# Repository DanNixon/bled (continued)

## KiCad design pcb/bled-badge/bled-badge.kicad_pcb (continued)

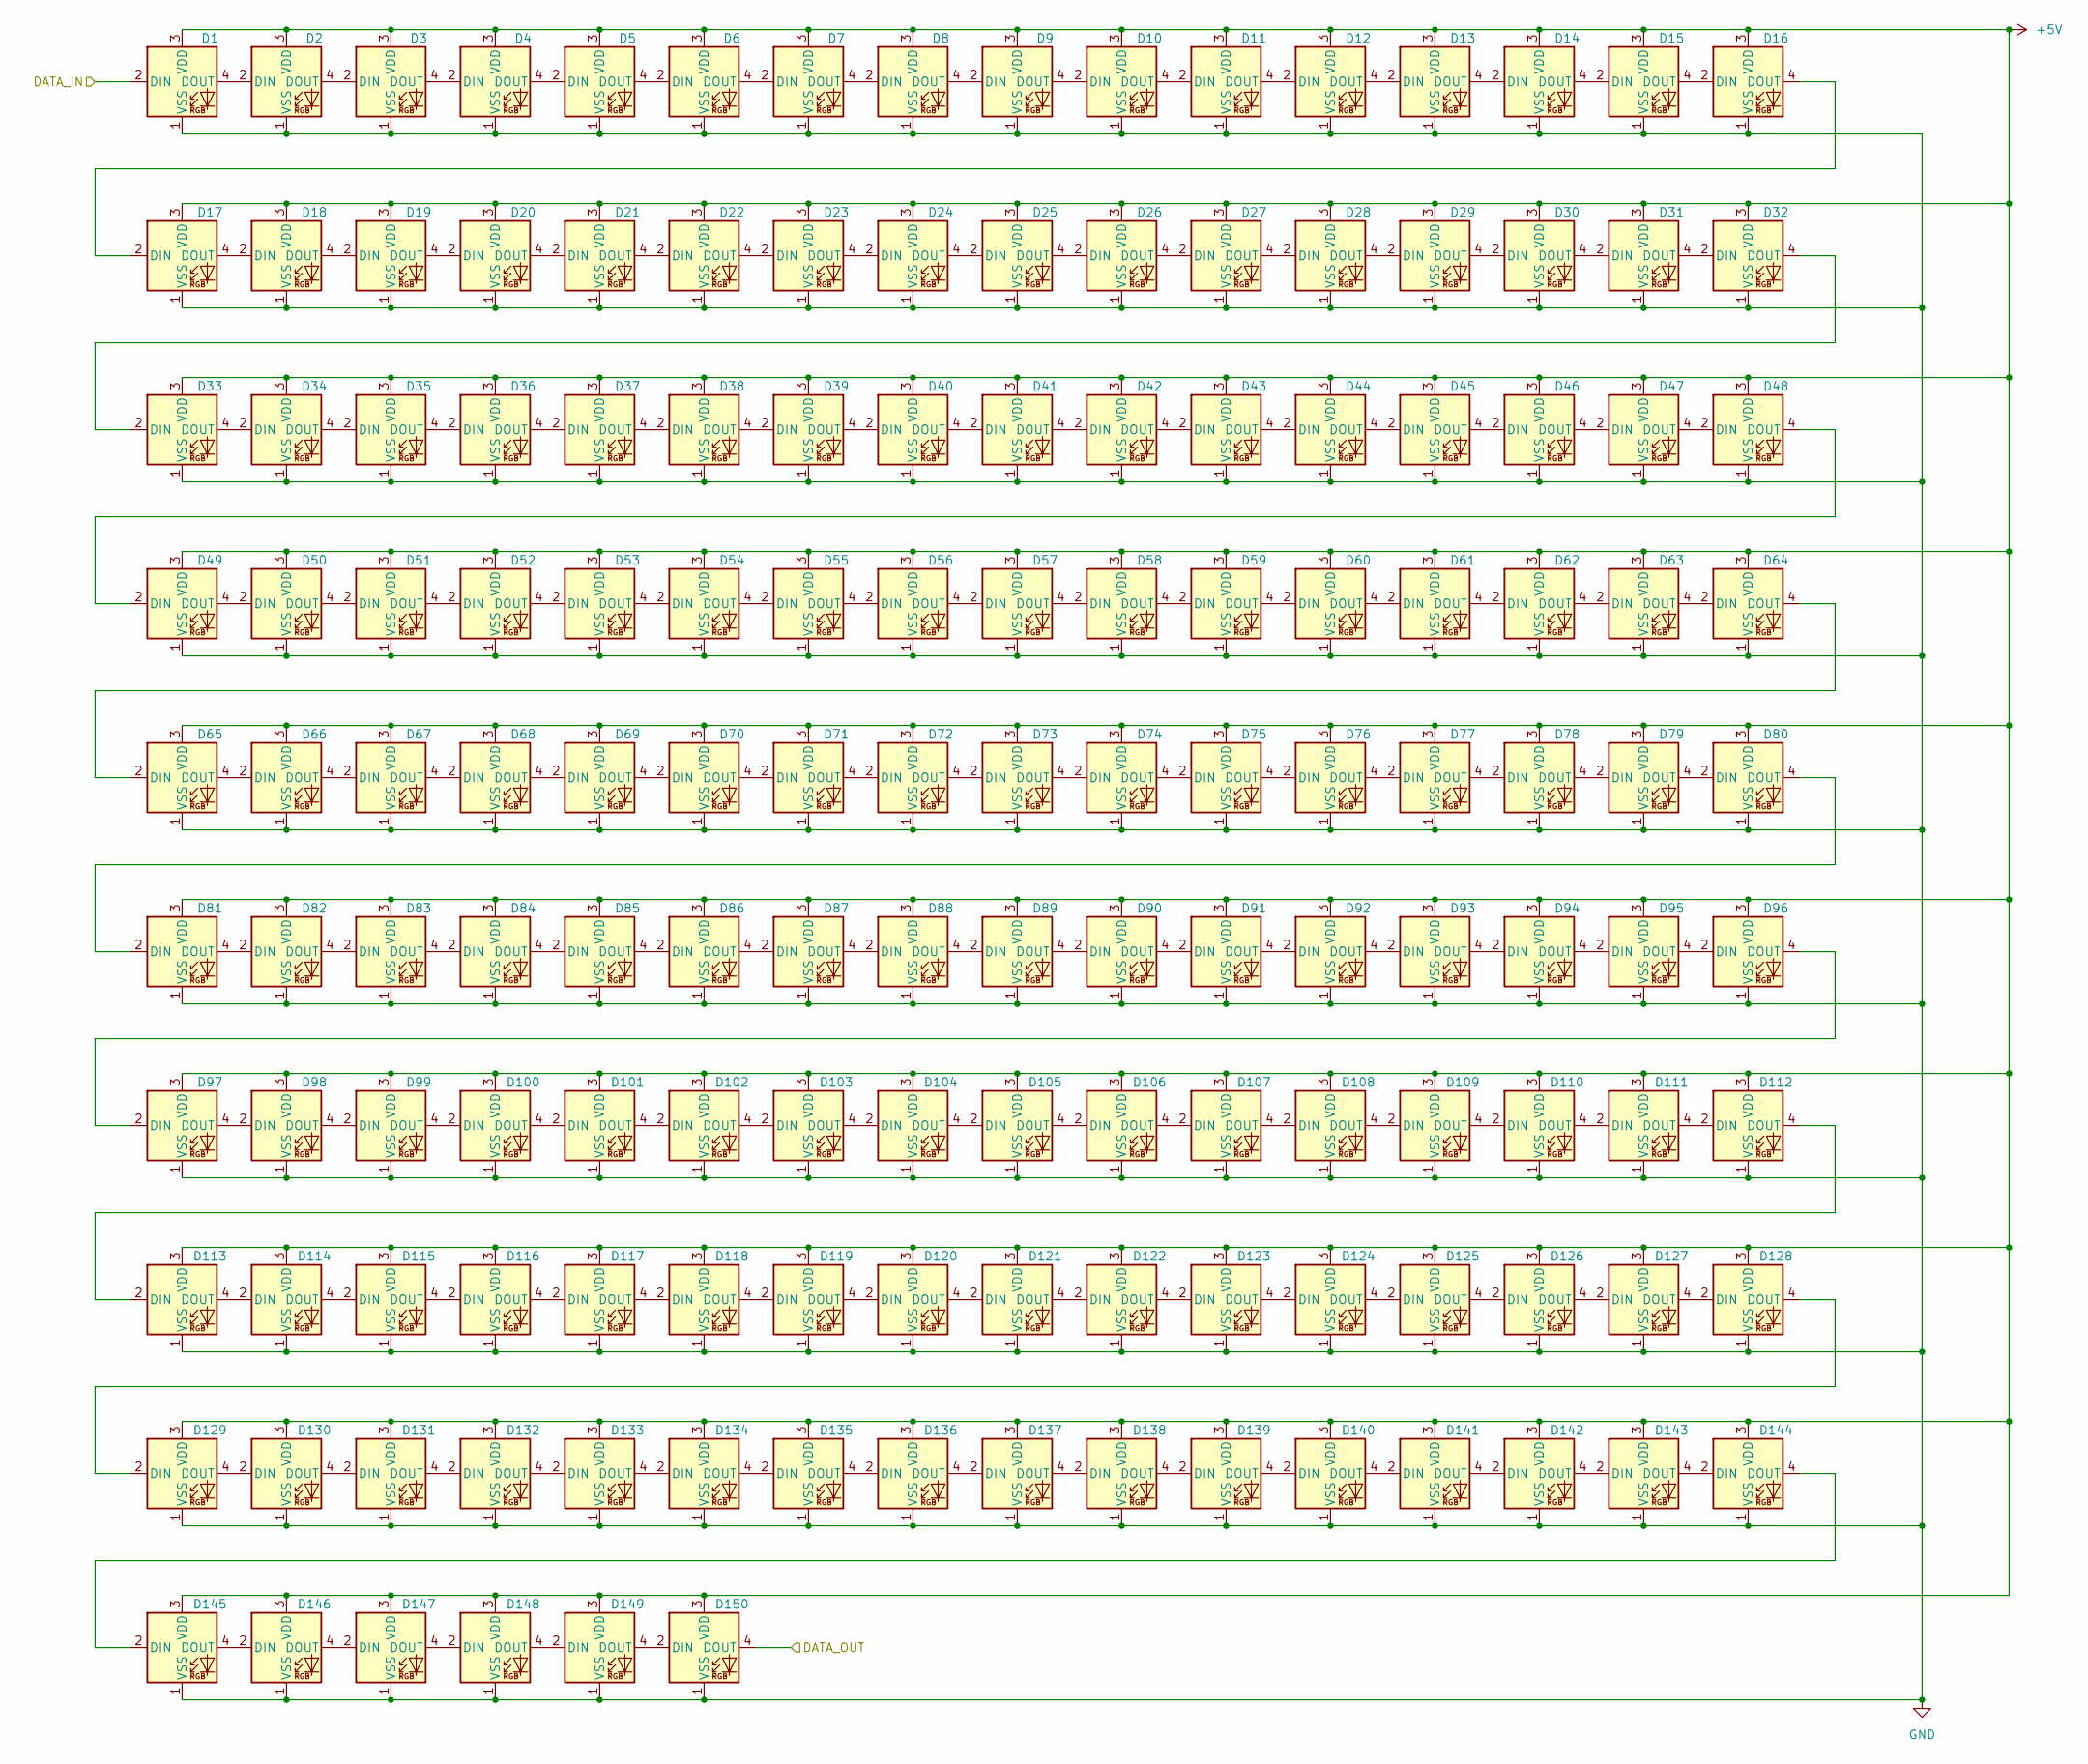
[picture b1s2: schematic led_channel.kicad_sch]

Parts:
D1, D2, D3, D4, D5, D6, D7, D8, D9, D10, D11, D12, D13, D14, D15, D16, D17, D18, D19, D20, D21, D22, D23, D24, D25, D26, D27, D28, D29, D30, D31, D32, D33, D34, D35, D36, D37, D38, D39, D40, D41, D42, D43, D44, D45, D46, D47, D48, D49, D50, D51, D52, D53, D54, D55, D56, D57, D58, D59, D60, D61, D62, D63, D64, D65, D66, D67, D68, D69, D70, D71, D72, D73, D74, D75, D76, D77, D78, D79, D80, D81, D82, D83, D84, D85, D86, D87, D88, D89, D90, D91, D92, D93, D94, D95, D96, D97, D98, D99, D100, D101, D102, D103, D104, D105, D106, D107, D108, D109, D110, D111, D112, D113, D114, D115, D116, D117, D118, D119, D120, D121, D122, D123, D124, D125, D126, D127, D128, D129, D130, D131, D132, D133, D134, D135, D136, D137, D138, D139, D140, D141, D142, D143, D144, D145, D146, D147, D148, D149, D150: XL-1615RGBC-WS2812B-S; XL-1615RGBC-2812B-S; LCSC C41413180

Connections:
+5V: D1.3 (VDD), D2.3 (VDD), D3.3 (VDD), D4.3 (VDD), D5.3 (VDD), D6.3 (VDD), D7.3 (VDD), D8.3 (VDD), D9.3 (VDD), D10.3 (VDD), D11.3 (VDD), D12.3 (VDD), D13.3 (VDD), D14.3 (VDD), D15.3 (VDD), D16.3 (VDD), D17.3 (VDD), D18.3 (VDD), D19.3 (VDD), D20.3 (VDD), D21.3 (VDD), D22.3 (VDD), D23.3 (VDD), D24.3 (VDD), D25.3 (VDD), D26.3 (VDD), D27.3 (VDD), D28.3 (VDD), D29.3 (VDD), D30.3 (VDD), D31.3 (VDD), D32.3 (VDD), D33.3 (VDD), D34.3 (VDD), D35.3 (VDD), D36.3 (VDD), D37.3 (VDD), D38.3 (VDD), D39.3 (VDD), D40.3 (VDD), D41.3 (VDD), D42.3 (VDD), D43.3 (VDD), D44.3 (VDD), D45.3 (VDD), D46.3 (VDD), D47.3 (VDD), D48.3 (VDD), D49.3 (VDD), D50.3 (VDD), D51.3 (VDD), D52.3 (VDD), D53.3 (VDD), D54.3 (VDD), D55.3 (VDD), D56.3 (VDD), D57.3 (VDD), D58.3 (VDD), D59.3 (VDD), D60.3 (VDD), D61.3 (VDD), D62.3 (VDD), D63.3 (VDD), D64.3 (VDD), D65.3 (VDD), D66.3 (VDD), D67.3 (VDD), D68.3 (VDD), D69.3 (VDD), D70.3 (VDD), D71.3 (VDD), D72.3 (VDD), D73.3 (VDD), D74.3 (VDD), D75.3 (VDD), D76.3 (VDD), D77.3 (VDD), D78.3 (VDD), D79.3 (VDD), D80.3 (VDD)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; also elsewhere on the board
/CH0_OUT: D150.4 (DOUT)
/CH3_IN: D1.2 (DIN); also elsewhere on the board
GND: D1.1 (VSS), D2.1 (VSS), D3.1 (VSS), D4.1 (VSS), D5.1 (VSS), D6.1 (VSS), D7.1 (VSS), D8.1 (VSS), D9.1 (VSS), D10.1 (VSS), D11.1 (VSS), D12.1 (VSS), D13.1 (VSS), D14.1 (VSS), D15.1 (VSS), D16.1 (VSS), D17.1 (VSS), D18.1 (VSS), D19.1 (VSS), D20.1 (VSS), D21.1 (VSS), D22.1 (VSS), D23.1 (VSS), D24.1 (VSS), D25.1 (VSS), D26.1 (VSS), D27.1 (VSS), D28.1 (VSS), D29.1 (VSS), D30.1 (VSS), D31.1 (VSS), D32.1 (VSS), D33.1 (VSS), D34.1 (VSS), D35.1 (VSS), D36.1 (VSS), D37.1 (VSS), D38.1 (VSS), D39.1 (VSS), D40.1 (VSS), D41.1 (VSS), D42.1 (VSS), D43.1 (VSS), D44.1 (VSS), D45.1 (VSS), D46.1 (VSS), D47.1 (VSS), D48.1 (VSS), D49.1 (VSS), D50.1 (VSS), D51.1 (VSS), D52.1 (VSS), D53.1 (VSS), D54.1 (VSS), D55.1 (VSS), D56.1 (VSS), D57.1 (VSS), D58.1 (VSS), D59.1 (VSS), D60.1 (VSS), D61.1 (VSS), D62.1 (VSS), D63.1 (VSS), D64.1 (VSS), D65.1 (VSS), D66.1 (VSS), D67.1 (VSS), D68.1 (VSS), D69.1 (VSS), D70.1 (VSS), D71.1 (VSS), D72.1 (VSS), D73.1 (VSS), D74.1 (VSS), D75.1 (VSS), D76.1 (VSS), D77.1 (VSS), D78.1 (VSS), D79.1 (VSS), D80.1 (VSS)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; also elsewhere on the board
unnamed: D1.4 (DOUT), D2.2 (DIN)
unnamed: D2.4 (DOUT), D3.2 (DIN)
unnamed: D3.4 (DOUT), D4.2 (DIN)
unnamed: D4.4 (DOUT), D5.2 (DIN)
unnamed: D5.4 (DOUT), D6.2 (DIN)
unnamed: D6.4 (DOUT), D7.2 (DIN)
unnamed: D7.4 (DOUT), D8.2 (DIN)
unnamed: D8.4 (DOUT), D9.2 (DIN)
unnamed: D9.4 (DOUT), D10.2 (DIN)
unnamed: D10.4 (DOUT), D11.2 (DIN)
unnamed: D11.4 (DOUT), D12.2 (DIN)
unnamed: D12.4 (DOUT), D13.2 (DIN)
unnamed: D13.4 (DOUT), D14.2 (DIN)
unnamed: D14.4 (DOUT), D15.2 (DIN)
unnamed: D15.4 (DOUT), D16.2 (DIN)
unnamed: D16.4 (DOUT), D17.2 (DIN)
unnamed: D17.4 (DOUT), D18.2 (DIN)
unnamed: D18.4 (DOUT), D19.2 (DIN)
unnamed: D19.4 (DOUT), D20.2 (DIN)
unnamed: D20.4 (DOUT), D21.2 (DIN)
unnamed: D21.4 (DOUT), D22.2 (DIN)
unnamed: D22.4 (DOUT), D23.2 (DIN)
unnamed: D23.4 (DOUT), D24.2 (DIN)
unnamed: D24.4 (DOUT), D25.2 (DIN)
unnamed: D25.4 (DOUT), D26.2 (DIN)
unnamed: D26.4 (DOUT), D27.2 (DIN)
unnamed: D27.4 (DOUT), D28.2 (DIN)
unnamed: D28.4 (DOUT), D29.2 (DIN)
unnamed: D29.4 (DOUT), D30.2 (DIN)
unnamed: D30.4 (DOUT), D31.2 (DIN)
unnamed: D31.4 (DOUT), D32.2 (DIN)
unnamed: D32.4 (DOUT), D33.2 (DIN)
unnamed: D33.4 (DOUT), D34.2 (DIN)
unnamed: D34.4 (DOUT), D35.2 (DIN)
unnamed: D35.4 (DOUT), D36.2 (DIN)
unnamed: D36.4 (DOUT), D37.2 (DIN)
unnamed: D37.4 (DOUT), D38.2 (DIN)
unnamed: D38.4 (DOUT), D39.2 (DIN)
unnamed: D39.4 (DOUT), D40.2 (DIN)
unnamed: D40.4 (DOUT), D41.2 (DIN)
unnamed: D41.4 (DOUT), D42.2 (DIN)
unnamed: D42.4 (DOUT), D43.2 (DIN)
unnamed: D43.4 (DOUT), D44.2 (DIN)
unnamed: D44.4 (DOUT), D45.2 (DIN)
unnamed: D45.4 (DOUT), D46.2 (DIN)
unnamed: D46.4 (DOUT), D47.2 (DIN)
unnamed: D47.4 (DOUT), D48.2 (DIN)
unnamed: D48.4 (DOUT), D49.2 (DIN)
unnamed: D49.4 (DOUT), D50.2 (DIN)
unnamed: D50.4 (DOUT), D51.2 (DIN)
unnamed: D51.4 (DOUT), D52.2 (DIN)
unnamed: D52.4 (DOUT), D53.2 (DIN)
unnamed: D53.4 (DOUT), D54.2 (DIN)
unnamed: D54.4 (DOUT), D55.2 (DIN)
unnamed: D55.4 (DOUT), D56.2 (DIN)
unnamed: D56.4 (DOUT), D57.2 (DIN)
unnamed: D57.4 (DOUT), D58.2 (DIN)
unnamed: D58.4 (DOUT), D59.2 (DIN)
unnamed: D59.4 (DOUT), D60.2 (DIN)
unnamed: D60.4 (DOUT), D61.2 (DIN)
unnamed: D61.4 (DOUT), D62.2 (DIN)
unnamed: D62.4 (DOUT), D63.2 (DIN)
unnamed: D63.4 (DOUT), D64.2 (DIN)
unnamed: D64.4 (DOUT), D65.2 (DIN)
unnamed: D65.4 (DOUT), D66.2 (DIN)
unnamed: D66.4 (DOUT), D67.2 (DIN)
unnamed: D67.4 (DOUT), D68.2 (DIN)
unnamed: D68.4 (DOUT), D69.2 (DIN)
unnamed: D69.4 (DOUT), D70.2 (DIN)
unnamed: D70.4 (DOUT), D71.2 (DIN)
unnamed: D71.4 (DOUT), D72.2 (DIN)
unnamed: D72.4 (DOUT), D73.2 (DIN)
unnamed: D73.4 (DOUT), D74.2 (DIN)
unnamed: D74.4 (DOUT), D75.2 (DIN)
unnamed: D75.4 (DOUT), D76.2 (DIN)
unnamed: D76.4 (DOUT), D77.2 (DIN)
unnamed: D77.4 (DOUT), D78.2 (DIN)
unnamed: D78.4 (DOUT), D79.2 (DIN)
unnamed: D79.4 (DOUT), D80.2 (DIN)
unnamed: D80.4 (DOUT), D81.2 (DIN)
unnamed: D81.4 (DOUT), D82.2 (DIN)
unnamed: D82.4 (DOUT), D83.2 (DIN)
unnamed: D83.4 (DOUT), D84.2 (DIN)
unnamed: D84.4 (DOUT), D85.2 (DIN)
unnamed: D85.4 (DOUT), D86.2 (DIN)
unnamed: D86.4 (DOUT), D87.2 (DIN)
unnamed: D87.4 (DOUT), D88.2 (DIN)
unnamed: D88.4 (DOUT), D89.2 (DIN)
unnamed: D89.4 (DOUT), D90.2 (DIN)
unnamed: D90.4 (DOUT), D91.2 (DIN)
unnamed: D91.4 (DOUT), D92.2 (DIN)
unnamed: D92.4 (DOUT), D93.2 (DIN)
unnamed: D93.4 (DOUT), D94.2 (DIN)
unnamed: D94.4 (DOUT), D95.2 (DIN)
unnamed: D95.4 (DOUT), D96.2 (DIN)
unnamed: D96.4 (DOUT), D97.2 (DIN)
unnamed: D97.4 (DOUT), D98.2 (DIN)
unnamed: D98.4 (DOUT), D99.2 (DIN)
unnamed: D99.4 (DOUT), D100.2 (DIN)
unnamed: D100.4 (DOUT), D101.2 (DIN)
unnamed: D101.4 (DOUT), D102.2 (DIN)
unnamed: D102.4 (DOUT), D103.2 (DIN)
unnamed: D103.4 (DOUT), D104.2 (DIN)
unnamed: D104.4 (DOUT), D105.2 (DIN)
unnamed: D105.4 (DOUT), D106.2 (DIN)
unnamed: D106.4 (DOUT), D107.2 (DIN)
unnamed: D107.4 (DOUT), D108.2 (DIN)
unnamed: D108.4 (DOUT), D109.2 (DIN)
unnamed: D109.4 (DOUT), D110.2 (DIN)
unnamed: D110.4 (DOUT), D111.2 (DIN)
unnamed: D111.4 (DOUT), D112.2 (DIN)
unnamed: D112.4 (DOUT), D113.2 (DIN)
unnamed: D113.4 (DOUT), D114.2 (DIN)
unnamed: D114.4 (DOUT), D115.2 (DIN)
unnamed: D115.4 (DOUT), D116.2 (DIN)
unnamed: D116.4 (DOUT), D117.2 (DIN)
unnamed: D117.4 (DOUT), D118.2 (DIN)
unnamed: D118.4 (DOUT), D119.2 (DIN)
unnamed: D119.4 (DOUT), D120.2 (DIN)
unnamed: D120.4 (DOUT), D121.2 (DIN)
unnamed: D121.4 (DOUT), D122.2 (DIN)
unnamed: D122.4 (DOUT), D123.2 (DIN)
unnamed: D123.4 (DOUT), D124.2 (DIN)
unnamed: D124.4 (DOUT), D125.2 (DIN)
unnamed: D125.4 (DOUT), D126.2 (DIN)
unnamed: D126.4 (DOUT), D127.2 (DIN)
unnamed: D127.4 (DOUT), D128.2 (DIN)
unnamed: D128.4 (DOUT), D129.2 (DIN)
unnamed: D129.4 (DOUT), D130.2 (DIN)
unnamed: D130.4 (DOUT), D131.2 (DIN)
unnamed: D131.4 (DOUT), D132.2 (DIN)
unnamed: D132.4 (DOUT), D133.2 (DIN)
unnamed: D133.4 (DOUT), D134.2 (DIN)
unnamed: D134.4 (DOUT), D135.2 (DIN)
unnamed: D135.4 (DOUT), D136.2 (DIN)
unnamed: D136.4 (DOUT), D137.2 (DIN)
unnamed: D137.4 (DOUT), D138.2 (DIN)
unnamed: D138.4 (DOUT), D139.2 (DIN)
unnamed: D139.4 (DOUT), D140.2 (DIN)
unnamed: D140.4 (DOUT), D141.2 (DIN)
unnamed: D141.4 (DOUT), D142.2 (DIN)
unnamed: D142.4 (DOUT), D143.2 (DIN)
unnamed: D143.4 (DOUT), D144.2 (DIN)
unnamed: D144.4 (DOUT), D145.2 (DIN)
unnamed: D145.4 (DOUT), D146.2 (DIN)
unnamed: D146.4 (DOUT), D147.2 (DIN)
unnamed: D147.4 (DOUT), D148.2 (DIN)
unnamed: D148.4 (DOUT), D149.2 (DIN)
unnamed: D149.4 (DOUT), D150.2 (DIN)

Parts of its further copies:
D151, D152, D153, D154, D155, D156, D157, D158, D159, D160, D161, D162, D163, D164, D165, D166, D167, D168, D169, D170, D171, D172, D173, D174, D175, D176, D177, D178, D179, D180, D181, D182, D183, D184, D185, D186, D187, D188, D189, D190, D191, D192, D193, D194, D195, D196, D197, D198, D199, D200, D201, D202, D203, D204, D205, D206, D207, D208, D209, D210, D211, D212, D213, D214, D215, D216, D217, D218, D219, D220, D221, D222, D223, D224, D225, D226, D227, D228, D229, D230, D231, D232, D233, D234, D235, D236, D237, D238, D239, D240, D241, D242, D243, D244, D245, D246, D247, D248, D249, D250, D251, D252, D253, D254, D255, D256, D257, D258, D259, D260, D261, D262, D263, D264, D265, D266, D267, D268, D269, D270, D271, D272, D273, D274, D275, D276, D277, D278, D279, D280, D281, D282, D283, D284, D285, D286, D287, D288, D289, D290, D291, D292, D293, D294, D295, D296, D297, D298, D299, D300, D301, D302, D303, D304, D305, D306, D307, D308, D309, D310, D311, D312, D313, D314, D315, D316, D317, D318, D319, D320, D321, D322, D323, D324, D325, D326, D327, D328, D329, D330, D331, D332, D333, D334, D335, D336, D337, D338, D339, D340, D341, D342, D343, D344, D345, D346, D347, D348, D349, D350, D351, D352, D353, D354, D355, D356, D357, D358, D359, D360, D361, D362, D363, D364, D365, D366, D367, D368, D369, D370, D371, D372, D373, D374, D375, D376, D377, D378, D379, D380, D381, D382, D383, D384, D385, D386, D387, D388, D389, D390, D391, D392, D393, D394, D395, D396, D397, D398, D399, D400, D401, D402, D403, D404, D405, D406, D407, D408, D409, D410, D411, D412, D413, D414, D415, D416, D417, D418, D419, D420, D421, D422, D423, D424, D425, D426, D427, D428, D429, D430, D431, D432, D433, D434, D435, D436, D437, D438, D439, D440, D441, D442, D443, D444, D445, D446, D447, D448, D449, D450, D451, D452, D453, D454, D455, D456, D457, D458, D459, D460, D461, D462, D463, D464, D465, D466, D467, D468, D469, D470, D471, D472, D473, D474, D475, D476, D477, D478, D479, D480, D481, D482, D483, D484, D485, D486, D487, D488, D489, D490, D491, D492, D493, D494, D495, D496, D497, D498, D499, D500, D501, D502, D503, D504, D505, D506, D507, D508, D509, D510, D511, D512, D513, D514, D515, D516, D517, D518, D519, D520, D521, D522, D523, D524, D525, D526, D527, D528, D529, D530, D531, D532, D533, D534, D535, D536, D537, D538, D539, D540, D541, D542, D543, D544, D545, D546, D547, D548, D549, D550, D551, D552, D553, D554, D555, D556, D557, D558, D559, D560, D561, D562, D563, D564, D565, D566, D567, D568, D569, D570, D571, D572, D573, D574, D575, D576, D577, D578, D579, D580, D581, D582, D583, D584, D585, D586, D587, D588, D589, D590, D591, D592, D593, D594, D595, D596, D597, D598, D599, D600: XL-1615RGBC-WS2812B-S; XL-1615RGBC-2812B-S; LCSC C41413180

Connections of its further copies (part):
+5V: D151.3 (VDD), D152.3 (VDD), D153.3 (VDD), D154.3 (VDD), D155.3 (VDD), D156.3 (VDD), D157.3 (VDD), D158.3 (VDD), D159.3 (VDD), D160.3 (VDD), D161.3 (VDD), D162.3 (VDD), D163.3 (VDD), D164.3 (VDD), D165.3 (VDD), D166.3 (VDD), D167.3 (VDD), D168.3 (VDD), D169.3 (VDD), D170.3 (VDD), D171.3 (VDD), D172.3 (VDD), D173.3 (VDD), D174.3 (VDD), D175.3 (VDD), D176.3 (VDD), D177.3 (VDD), D178.3 (VDD), D179.3 (VDD), D180.3 (VDD), D181.3 (VDD), D182.3 (VDD), D183.3 (VDD), D184.3 (VDD), D185.3 (VDD), D186.3 (VDD), D187.3 (VDD), D188.3 (VDD), D189.3 (VDD), D190.3 (VDD), D191.3 (VDD), D192.3 (VDD), D193.3 (VDD), D194.3 (VDD), D195.3 (VDD), D196.3 (VDD), D197.3 (VDD), D198.3 (VDD), D199.3 (VDD), D200.3 (VDD), D201.3 (VDD), D202.3 (VDD), D203.3 (VDD), D204.3 (VDD), D205.3 (VDD), D206.3 (VDD), D207.3 (VDD), D208.3 (VDD), D209.3 (VDD), D210.3 (VDD), D211.3 (VDD), D212.3 (VDD), D213.3 (VDD), D214.3 (VDD), D215.3 (VDD), D216.3 (VDD), D217.3 (VDD), D218.3 (VDD), D219.3 (VDD), D220.3 (VDD), D221.3 (VDD), D222.3 (VDD), D223.3 (VDD), D224.3 (VDD), D225.3 (VDD), D226.3 (VDD), D227.3 (VDD), D228.3 (VDD), D229.3 (VDD), D230.3 (VDD)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; also elsewhere on the board
/CH0_IN: D451.2 (DIN); also elsewhere on the board
/CH1_IN: D151.2 (DIN); also elsewhere on the board
/CH1_OUT: D300.4 (DOUT)
/CH2_IN: D301.2 (DIN); also elsewhere on the board
/CH2_OUT: D450.4 (DOUT)
/CH3_OUT: D600.4 (DOUT)
GND: D151.1 (VSS), D152.1 (VSS), D153.1 (VSS), D154.1 (VSS), D155.1 (VSS), D156.1 (VSS), D157.1 (VSS), D158.1 (VSS), D159.1 (VSS), D160.1 (VSS), D161.1 (VSS), D162.1 (VSS), D163.1 (VSS), D164.1 (VSS), D165.1 (VSS), D166.1 (VSS), D167.1 (VSS), D168.1 (VSS), D169.1 (VSS), D170.1 (VSS), D171.1 (VSS), D172.1 (VSS), D173.1 (VSS), D174.1 (VSS), D175.1 (VSS), D176.1 (VSS), D177.1 (VSS), D178.1 (VSS), D179.1 (VSS), D180.1 (VSS), D181.1 (VSS), D182.1 (VSS), D183.1 (VSS), D184.1 (VSS), D185.1 (VSS), D186.1 (VSS), D187.1 (VSS), D188.1 (VSS), D189.1 (VSS), D190.1 (VSS), D191.1 (VSS), D192.1 (VSS), D193.1 (VSS), D194.1 (VSS), D195.1 (VSS), D196.1 (VSS), D197.1 (VSS), D198.1 (VSS), D199.1 (VSS), D200.1 (VSS), D201.1 (VSS), D202.1 (VSS), D203.1 (VSS), D204.1 (VSS), D205.1 (VSS), D206.1 (VSS), D207.1 (VSS), D208.1 (VSS), D209.1 (VSS), D210.1 (VSS), D211.1 (VSS), D212.1 (VSS), D213.1 (VSS), D214.1 (VSS), D215.1 (VSS), D216.1 (VSS), D217.1 (VSS), D218.1 (VSS), D219.1 (VSS), D220.1 (VSS), D221.1 (VSS), D222.1 (VSS), D223.1 (VSS), D224.1 (VSS), D225.1 (VSS), D226.1 (VSS), D227.1 (VSS), D228.1 (VSS), D229.1 (VSS), D230.1 (VSS)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; also elsewhere on the board
unnamed: D151.4 (DOUT), D152.2 (DIN)
unnamed: D152.4 (DOUT), D153.2 (DIN)
unnamed: D153.4 (DOUT), D154.2 (DIN)
unnamed: D154.4 (DOUT), D155.2 (DIN)
unnamed: D155.4 (DOUT), D156.2 (DIN)
unnamed: D156.4 (DOUT), D157.2 (DIN)
unnamed: D157.4 (DOUT), D158.2 (DIN)
unnamed: D158.4 (DOUT), D159.2 (DIN)
unnamed: D159.4 (DOUT), D160.2 (DIN)
unnamed: D160.4 (DOUT), D161.2 (DIN)
unnamed: D161.4 (DOUT), D162.2 (DIN)
unnamed: D162.4 (DOUT), D163.2 (DIN)
unnamed: D163.4 (DOUT), D164.2 (DIN)
unnamed: D164.4 (DOUT), D165.2 (DIN)
unnamed: D165.4 (DOUT), D166.2 (DIN)
unnamed: D166.4 (DOUT), D167.2 (DIN)
unnamed: D167.4 (DOUT), D168.2 (DIN)
unnamed: D168.4 (DOUT), D169.2 (DIN)
unnamed: D169.4 (DOUT), D170.2 (DIN)
unnamed: D170.4 (DOUT), D171.2 (DIN)
unnamed: D171.4 (DOUT), D172.2 (DIN)
unnamed: D172.4 (DOUT), D173.2 (DIN)
unnamed: D173.4 (DOUT), D174.2 (DIN)
unnamed: D174.4 (DOUT), D175.2 (DIN)
unnamed: D175.4 (DOUT), D176.2 (DIN)
unnamed: D176.4 (DOUT), D177.2 (DIN)
unnamed: D177.4 (DOUT), D178.2 (DIN)
unnamed: D178.4 (DOUT), D179.2 (DIN)
unnamed: D179.4 (DOUT), D180.2 (DIN)
unnamed: D180.4 (DOUT), D181.2 (DIN)
unnamed: D181.4 (DOUT), D182.2 (DIN)
unnamed: D182.4 (DOUT), D183.2 (DIN)
unnamed: D183.4 (DOUT), D184.2 (DIN)
unnamed: D184.4 (DOUT), D185.2 (DIN)
unnamed: D185.4 (DOUT), D186.2 (DIN)
unnamed: D186.4 (DOUT), D187.2 (DIN)
unnamed: D187.4 (DOUT), D188.2 (DIN)
unnamed: D188.4 (DOUT), D189.2 (DIN)
unnamed: D189.4 (DOUT), D190.2 (DIN)
unnamed: D190.4 (DOUT), D191.2 (DIN)
unnamed: D191.4 (DOUT), D192.2 (DIN)
unnamed: D192.4 (DOUT), D193.2 (DIN)
unnamed: D193.4 (DOUT), D194.2 (DIN)
unnamed: D194.4 (DOUT), D195.2 (DIN)
unnamed: D195.4 (DOUT), D196.2 (DIN)
unnamed: D196.4 (DOUT), D197.2 (DIN)
unnamed: D197.4 (DOUT), D198.2 (DIN)
unnamed: D198.4 (DOUT), D199.2 (DIN)
unnamed: D199.4 (DOUT), D200.2 (DIN)
unnamed: D200.4 (DOUT), D201.2 (DIN)
unnamed: D201.4 (DOUT), D202.2 (DIN)
unnamed: D202.4 (DOUT), D203.2 (DIN)
unnamed: D203.4 (DOUT), D204.2 (DIN)
unnamed: D204.4 (DOUT), D205.2 (DIN)
unnamed: D205.4 (DOUT), D206.2 (DIN)
unnamed: D206.4 (DOUT), D207.2 (DIN)
unnamed: D207.4 (DOUT), D208.2 (DIN)
unnamed: D208.4 (DOUT), D209.2 (DIN)
unnamed: D209.4 (DOUT), D210.2 (DIN)
unnamed: D210.4 (DOUT), D211.2 (DIN)
unnamed: D211.4 (DOUT), D212.2 (DIN)
unnamed: D212.4 (DOUT), D213.2 (DIN)
unnamed: D213.4 (DOUT), D214.2 (DIN)
unnamed: D214.4 (DOUT), D215.2 (DIN)
unnamed: D215.4 (DOUT), D216.2 (DIN)
unnamed: D216.4 (DOUT), D217.2 (DIN)
unnamed: D217.4 (DOUT), D218.2 (DIN)
unnamed: D218.4 (DOUT), D219.2 (DIN)
unnamed: D219.4 (DOUT), D220.2 (DIN)
unnamed: D220.4 (DOUT), D221.2 (DIN)
unnamed: D221.4 (DOUT), D222.2 (DIN)
unnamed: D222.4 (DOUT), D223.2 (DIN)
unnamed: D223.4 (DOUT), D224.2 (DIN)
unnamed: D224.4 (DOUT), D225.2 (DIN)
unnamed: D225.4 (DOUT), D226.2 (DIN)
unnamed: D226.4 (DOUT), D227.2 (DIN)
unnamed: D227.4 (DOUT), D228.2 (DIN)
unnamed: D228.4 (DOUT), D229.2 (DIN)
unnamed: D229.4 (DOUT), D230.2 (DIN)
unnamed: D230.4 (DOUT), D231.2 (DIN)
unnamed: D231.4 (DOUT), D232.2 (DIN)
unnamed: D232.4 (DOUT), D233.2 (DIN)
unnamed: D233.4 (DOUT), D234.2 (DIN)
unnamed: D234.4 (DOUT), D235.2 (DIN)
unnamed: D235.4 (DOUT), D236.2 (DIN)
unnamed: D236.4 (DOUT), D237.2 (DIN)
unnamed: D237.4 (DOUT), D238.2 (DIN)
unnamed: D238.4 (DOUT), D239.2 (DIN)
unnamed: D239.4 (DOUT), D240.2 (DIN)
unnamed: D240.4 (DOUT), D241.2 (DIN)
unnamed: D241.4 (DOUT), D242.2 (DIN)
unnamed: D242.4 (DOUT), D243.2 (DIN)
unnamed: D243.4 (DOUT), D244.2 (DIN)
unnamed: D244.4 (DOUT), D245.2 (DIN)
unnamed: D245.4 (DOUT), D246.2 (DIN)
unnamed: D246.4 (DOUT), D247.2 (DIN)
unnamed: D247.4 (DOUT), D248.2 (DIN)
unnamed: D248.4 (DOUT), D249.2 (DIN)
unnamed: D249.4 (DOUT), D250.2 (DIN)
unnamed: D250.4 (DOUT), D251.2 (DIN)
unnamed: D251.4 (DOUT), D252.2 (DIN)
unnamed: D252.4 (DOUT), D253.2 (DIN)
unnamed: D253.4 (DOUT), D254.2 (DIN)
unnamed: D254.4 (DOUT), D255.2 (DIN)
unnamed: D255.4 (DOUT), D256.2 (DIN)
unnamed: D256.4 (DOUT), D257.2 (DIN)
unnamed: D257.4 (DOUT), D258.2 (DIN)
unnamed: D258.4 (DOUT), D259.2 (DIN)
unnamed: D259.4 (DOUT), D260.2 (DIN)
unnamed: D260.4 (DOUT), D261.2 (DIN)
unnamed: D261.4 (DOUT), D262.2 (DIN)
unnamed: D262.4 (DOUT), D263.2 (DIN)
unnamed: D263.4 (DOUT), D264.2 (DIN)
unnamed: D264.4 (DOUT), D265.2 (DIN)
unnamed: D265.4 (DOUT), D266.2 (DIN)
unnamed: D266.4 (DOUT), D267.2 (DIN)
unnamed: D267.4 (DOUT), D268.2 (DIN)
unnamed: D268.4 (DOUT), D269.2 (DIN)
unnamed: D269.4 (DOUT), D270.2 (DIN)
unnamed: D270.4 (DOUT), D271.2 (DIN)
unnamed: D271.4 (DOUT), D272.2 (DIN)
unnamed: D272.4 (DOUT), D273.2 (DIN)
unnamed: D273.4 (DOUT), D274.2 (DIN)
unnamed: D274.4 (DOUT), D275.2 (DIN)
unnamed: D275.4 (DOUT), D276.2 (DIN)
unnamed: D276.4 (DOUT), D277.2 (DIN)
unnamed: D277.4 (DOUT), D278.2 (DIN)
unnamed: D278.4 (DOUT), D279.2 (DIN)
unnamed: D279.4 (DOUT), D280.2 (DIN)
unnamed: D280.4 (DOUT), D281.2 (DIN)
unnamed: D281.4 (DOUT), D282.2 (DIN)
unnamed: D282.4 (DOUT), D283.2 (DIN)
unnamed: D283.4 (DOUT), D284.2 (DIN)
unnamed: D284.4 (DOUT), D285.2 (DIN)
unnamed: D285.4 (DOUT), D286.2 (DIN)
unnamed: D286.4 (DOUT), D287.2 (DIN)
unnamed: D287.4 (DOUT), D288.2 (DIN)
unnamed: D288.4 (DOUT), D289.2 (DIN)
unnamed: D289.4 (DOUT), D290.2 (DIN)
unnamed: D290.4 (DOUT), D291.2 (DIN)
unnamed: D291.4 (DOUT), D292.2 (DIN)
unnamed: D292.4 (DOUT), D293.2 (DIN)
unnamed: D293.4 (DOUT), D294.2 (DIN)
unnamed: D294.4 (DOUT), D295.2 (DIN)
unnamed: D295.4 (DOUT), D296.2 (DIN)
unnamed: D296.4 (DOUT), D297.2 (DIN)
unnamed: D297.4 (DOUT), D298.2 (DIN)
unnamed: D298.4 (DOUT), D299.2 (DIN)
unnamed: D299.4 (DOUT), D300.2 (DIN)
unnamed: D301.4 (DOUT), D302.2 (DIN)
unnamed: D302.4 (DOUT), D303.2 (DIN)
unnamed: D303.4 (DOUT), D304.2 (DIN)
unnamed: D304.4 (DOUT), D305.2 (DIN)
unnamed: D305.4 (DOUT), D306.2 (DIN)
unnamed: D306.4 (DOUT), D307.2 (DIN)
unnamed: D307.4 (DOUT), D308.2 (DIN)
unnamed: D308.4 (DOUT), D309.2 (DIN)
unnamed: D309.4 (DOUT), D310.2 (DIN)
unnamed: D310.4 (DOUT), D311.2 (DIN)
unnamed: D311.4 (DOUT), D312.2 (DIN)
unnamed: D312.4 (DOUT), D313.2 (DIN)
unnamed: D313.4 (DOUT), D314.2 (DIN)
unnamed: D314.4 (DOUT), D315.2 (DIN)
unnamed: D315.4 (DOUT), D316.2 (DIN)
unnamed: D316.4 (DOUT), D317.2 (DIN)
unnamed: D317.4 (DOUT), D318.2 (DIN)
unnamed: D318.4 (DOUT), D319.2 (DIN)
unnamed: D319.4 (DOUT), D320.2 (DIN)
unnamed: D320.4 (DOUT), D321.2 (DIN)
unnamed: D321.4 (DOUT), D322.2 (DIN)
unnamed: D322.4 (DOUT), D323.2 (DIN)
unnamed: D323.4 (DOUT), D324.2 (DIN)
unnamed: D324.4 (DOUT), D325.2 (DIN)
unnamed: D325.4 (DOUT), D326.2 (DIN)
unnamed: D326.4 (DOUT), D327.2 (DIN)
unnamed: D327.4 (DOUT), D328.2 (DIN)
unnamed: D328.4 (DOUT), D329.2 (DIN)
unnamed: D329.4 (DOUT), D330.2 (DIN)
unnamed: D330.4 (DOUT), D331.2 (DIN)
unnamed: D331.4 (DOUT), D332.2 (DIN)
unnamed: D332.4 (DOUT), D333.2 (DIN)
unnamed: D333.4 (DOUT), D334.2 (DIN)
unnamed: D334.4 (DOUT), D335.2 (DIN)
unnamed: D335.4 (DOUT), D336.2 (DIN)
unnamed: D336.4 (DOUT), D337.2 (DIN)
unnamed: D337.4 (DOUT), D338.2 (DIN)
unnamed: D338.4 (DOUT), D339.2 (DIN)
unnamed: D339.4 (DOUT), D340.2 (DIN)
unnamed: D340.4 (DOUT), D341.2 (DIN)
unnamed: D341.4 (DOUT), D342.2 (DIN)
unnamed: D342.4 (DOUT), D343.2 (DIN)
unnamed: D343.4 (DOUT), D344.2 (DIN)
unnamed: D344.4 (DOUT), D345.2 (DIN)
unnamed: D345.4 (DOUT), D346.2 (DIN)
unnamed: D346.4 (DOUT), D347.2 (DIN)
unnamed: D347.4 (DOUT), D348.2 (DIN)
unnamed: D348.4 (DOUT), D349.2 (DIN)
unnamed: D349.4 (DOUT), D350.2 (DIN)
unnamed: D350.4 (DOUT), D351.2 (DIN)
unnamed: D351.4 (DOUT), D352.2 (DIN)
unnamed: D352.4 (DOUT), D353.2 (DIN)
unnamed: D353.4 (DOUT), D354.2 (DIN)
unnamed: D354.4 (DOUT), D355.2 (DIN)
unnamed: D355.4 (DOUT), D356.2 (DIN)
unnamed: D356.4 (DOUT), D357.2 (DIN)
unnamed: D357.4 (DOUT), D358.2 (DIN)
unnamed: D358.4 (DOUT), D359.2 (DIN)
unnamed: D359.4 (DOUT), D360.2 (DIN)
unnamed: D360.4 (DOUT), D361.2 (DIN)
unnamed: D361.4 (DOUT), D362.2 (DIN)
unnamed: D362.4 (DOUT), D363.2 (DIN)
unnamed: D363.4 (DOUT), D364.2 (DIN)
unnamed: D364.4 (DOUT), D365.2 (DIN)
unnamed: D365.4 (DOUT), D366.2 (DIN)
unnamed: D366.4 (DOUT), D367.2 (DIN)
unnamed: D367.4 (DOUT), D368.2 (DIN)
unnamed: D368.4 (DOUT), D369.2 (DIN)
unnamed: D369.4 (DOUT), D370.2 (DIN)
unnamed: D370.4 (DOUT), D371.2 (DIN)
unnamed: D371.4 (DOUT), D372.2 (DIN)
unnamed: D372.4 (DOUT), D373.2 (DIN)
unnamed: D373.4 (DOUT), D374.2 (DIN)
unnamed: D374.4 (DOUT), D375.2 (DIN)
unnamed: D375.4 (DOUT), D376.2 (DIN)
unnamed: D376.4 (DOUT), D377.2 (DIN)
unnamed: D377.4 (DOUT), D378.2 (DIN)
unnamed: D378.4 (DOUT), D379.2 (DIN)
unnamed: D379.4 (DOUT), D380.2 (DIN)
unnamed: D380.4 (DOUT), D381.2 (DIN)
unnamed: D381.4 (DOUT), D382.2 (DIN)
unnamed: D382.4 (DOUT), D383.2 (DIN)
unnamed: D383.4 (DOUT), D384.2 (DIN)
unnamed: D384.4 (DOUT), D385.2 (DIN)
unnamed: D385.4 (DOUT), D386.2 (DIN)
unnamed: D386.4 (DOUT), D387.2 (DIN)
unnamed: D387.4 (DOUT), D388.2 (DIN)
unnamed: D388.4 (DOUT), D389.2 (DIN)
unnamed: D389.4 (DOUT), D390.2 (DIN)
unnamed: D390.4 (DOUT), D391.2 (DIN)
unnamed: D391.4 (DOUT), D392.2 (DIN)
unnamed: D392.4 (DOUT), D393.2 (DIN)
unnamed: D393.4 (DOUT), D394.2 (DIN)
unnamed: D394.4 (DOUT), D395.2 (DIN)
unnamed: D395.4 (DOUT), D396.2 (DIN)
unnamed: D396.4 (DOUT), D397.2 (DIN)
unnamed: D397.4 (DOUT), D398.2 (DIN)
unnamed: D398.4 (DOUT), D399.2 (DIN)
unnamed: D399.4 (DOUT), D400.2 (DIN)
unnamed: D400.4 (DOUT), D401.2 (DIN)
unnamed: D401.4 (DOUT), D402.2 (DIN)
unnamed: D402.4 (DOUT), D403.2 (DIN)
unnamed: D403.4 (DOUT), D404.2 (DIN)
unnamed: D404.4 (DOUT), D405.2 (DIN)
unnamed: D405.4 (DOUT), D406.2 (DIN)
unnamed: D406.4 (DOUT), D407.2 (DIN)
unnamed: D407.4 (DOUT), D408.2 (DIN)
unnamed: D408.4 (DOUT), D409.2 (DIN)
unnamed: D409.4 (DOUT), D410.2 (DIN)
unnamed: D410.4 (DOUT), D411.2 (DIN)
unnamed: D411.4 (DOUT), D412.2 (DIN)
unnamed: D412.4 (DOUT), D413.2 (DIN)
unnamed: D413.4 (DOUT), D414.2 (DIN)
unnamed: D414.4 (DOUT), D415.2 (DIN)
unnamed: D415.4 (DOUT), D416.2 (DIN)
unnamed: D416.4 (DOUT), D417.2 (DIN)
unnamed: D417.4 (DOUT), D418.2 (DIN)
unnamed: D418.4 (DOUT), D419.2 (DIN)
unnamed: D419.4 (DOUT), D420.2 (DIN)
unnamed: D420.4 (DOUT), D421.2 (DIN)
unnamed: D421.4 (DOUT), D422.2 (DIN)
unnamed: D422.4 (DOUT), D423.2 (DIN)
unnamed: D423.4 (DOUT), D424.2 (DIN)
unnamed: D424.4 (DOUT), D425.2 (DIN)
unnamed: D425.4 (DOUT), D426.2 (DIN)
unnamed: D426.4 (DOUT), D427.2 (DIN)
unnamed: D427.4 (DOUT), D428.2 (DIN)
unnamed: D428.4 (DOUT), D429.2 (DIN)
unnamed: D429.4 (DOUT), D430.2 (DIN)
unnamed: D430.4 (DOUT), D431.2 (DIN)
unnamed: D431.4 (DOUT), D432.2 (DIN)
unnamed: D432.4 (DOUT), D433.2 (DIN)
unnamed: D433.4 (DOUT), D434.2 (DIN)
unnamed: D434.4 (DOUT), D435.2 (DIN)
unnamed: D435.4 (DOUT), D436.2 (DIN)
unnamed: D436.4 (DOUT), D437.2 (DIN)
unnamed: D437.4 (DOUT), D438.2 (DIN)
unnamed: D438.4 (DOUT), D439.2 (DIN)
unnamed: D439.4 (DOUT), D440.2 (DIN)
unnamed: D440.4 (DOUT), D441.2 (DIN)
unnamed: D441.4 (DOUT), D442.2 (DIN)
unnamed: D442.4 (DOUT), D443.2 (DIN)
unnamed: D443.4 (DOUT), D444.2 (DIN)
unnamed: D444.4 (DOUT), D445.2 (DIN)
unnamed: D445.4 (DOUT), D446.2 (DIN)
unnamed: D446.4 (DOUT), D447.2 (DIN)
unnamed: D447.4 (DOUT), D448.2 (DIN)
unnamed: D448.4 (DOUT), D449.2 (DIN)
unnamed: D449.4 (DOUT), D450.2 (DIN)
unnamed: D451.4 (DOUT), D452.2 (DIN)
unnamed: D452.4 (DOUT), D453.2 (DIN)
unnamed: D453.4 (DOUT), D454.2 (DIN)
unnamed: D454.4 (DOUT), D455.2 (DIN)
unnamed: D455.4 (DOUT), D456.2 (DIN)
unnamed: D456.4 (DOUT), D457.2 (DIN)
unnamed: D457.4 (DOUT), D458.2 (DIN)
unnamed: D458.4 (DOUT), D459.2 (DIN)
unnamed: D459.4 (DOUT), D460.2 (DIN)
unnamed: D460.4 (DOUT), D461.2 (DIN)
unnamed: D461.4 (DOUT), D462.2 (DIN)
unnamed: D462.4 (DOUT), D463.2 (DIN)
unnamed: D463.4 (DOUT), D464.2 (DIN)
unnamed: D464.4 (DOUT), D465.2 (DIN)
unnamed: D465.4 (DOUT), D466.2 (DIN)
unnamed: D466.4 (DOUT), D467.2 (DIN)
unnamed: D467.4 (DOUT), D468.2 (DIN)
unnamed: D468.4 (DOUT), D469.2 (DIN)
unnamed: D469.4 (DOUT), D470.2 (DIN)
unnamed: D470.4 (DOUT), D471.2 (DIN)
unnamed: D471.4 (DOUT), D472.2 (DIN)
unnamed: D472.4 (DOUT), D473.2 (DIN)
unnamed: D473.4 (DOUT), D474.2 (DIN)
unnamed: D474.4 (DOUT), D475.2 (DIN)
unnamed: D475.4 (DOUT), D476.2 (DIN)
unnamed: D476.4 (DOUT), D477.2 (DIN)
unnamed: D477.4 (DOUT), D478.2 (DIN)
unnamed: D478.4 (DOUT), D479.2 (DIN)
unnamed: D479.4 (DOUT), D480.2 (DIN)
unnamed: D480.4 (DOUT), D481.2 (DIN)
unnamed: D481.4 (DOUT), D482.2 (DIN)
unnamed: D482.4 (DOUT), D483.2 (DIN)
unnamed: D483.4 (DOUT), D484.2 (DIN)
unnamed: D484.4 (DOUT), D485.2 (DIN)
unnamed: D485.4 (DOUT), D486.2 (DIN)
unnamed: D486.4 (DOUT), D487.2 (DIN)
unnamed: D487.4 (DOUT), D488.2 (DIN)
unnamed: D488.4 (DOUT), D489.2 (DIN)
unnamed: D489.4 (DOUT), D490.2 (DIN)
unnamed: D490.4 (DOUT), D491.2 (DIN)
unnamed: D491.4 (DOUT), D492.2 (DIN)
unnamed: D492.4 (DOUT), D493.2 (DIN)
unnamed: D493.4 (DOUT), D494.2 (DIN)
unnamed: D494.4 (DOUT), D495.2 (DIN)
unnamed: D495.4 (DOUT), D496.2 (DIN)
unnamed: D496.4 (DOUT), D497.2 (DIN)
unnamed: D497.4 (DOUT), D498.2 (DIN)
unnamed: D498.4 (DOUT), D499.2 (DIN)
unnamed: D499.4 (DOUT), D500.2 (DIN)
unnamed: D500.4 (DOUT), D501.2 (DIN)
unnamed: D501.4 (DOUT), D502.2 (DIN)
unnamed: D502.4 (DOUT), D503.2 (DIN)
unnamed: D503.4 (DOUT), D504.2 (DIN)
unnamed: D504.4 (DOUT), D505.2 (DIN)
unnamed: D505.4 (DOUT), D506.2 (DIN)
unnamed: D506.4 (DOUT), D507.2 (DIN)
unnamed: D507.4 (DOUT), D508.2 (DIN)
unnamed: D508.4 (DOUT), D509.2 (DIN)
unnamed: D509.4 (DOUT), D510.2 (DIN)
unnamed: D510.4 (DOUT), D511.2 (DIN)
unnamed: D511.4 (DOUT), D512.2 (DIN)
unnamed: D512.4 (DOUT), D513.2 (DIN)
unnamed: D513.4 (DOUT), D514.2 (DIN)
unnamed: D514.4 (DOUT), D515.2 (DIN)
unnamed: D515.4 (DOUT), D516.2 (DIN)
unnamed: D516.4 (DOUT), D517.2 (DIN)
unnamed: D517.4 (DOUT), D518.2 (DIN)
unnamed: D518.4 (DOUT), D519.2 (DIN)
unnamed: D519.4 (DOUT), D520.2 (DIN)
unnamed: D520.4 (DOUT), D521.2 (DIN)
unnamed: D521.4 (DOUT), D522.2 (DIN)
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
